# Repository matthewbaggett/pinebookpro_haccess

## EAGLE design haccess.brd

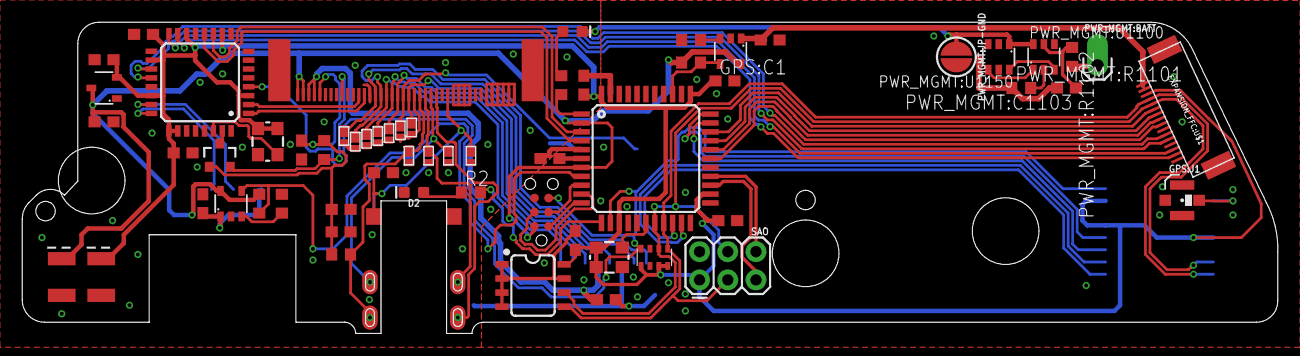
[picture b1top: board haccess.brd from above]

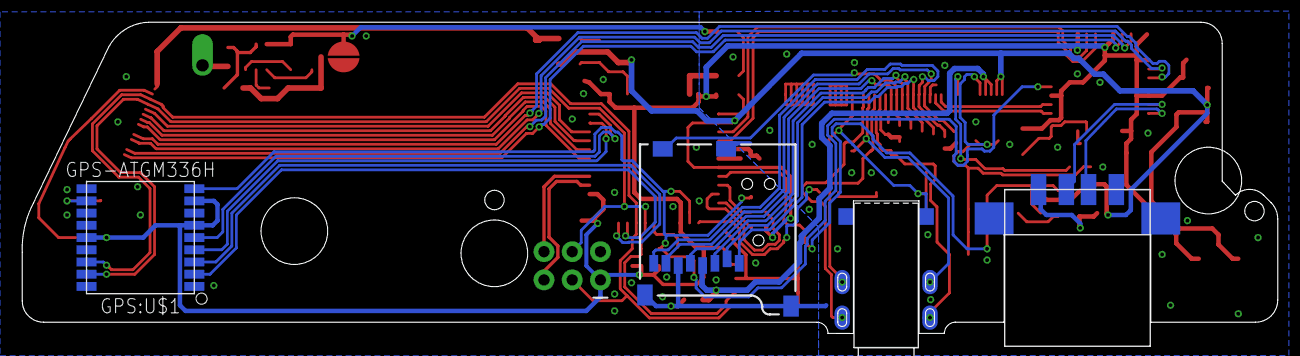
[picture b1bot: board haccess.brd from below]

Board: 2 copper layers, 113.0 x 28.0 mm, 65 parts (4 on the bottom side), 64 nets.

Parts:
D1, D2: LED-0603
EEPROM:C1: 0.1uF; C0603
EEPROM:EEPROM: 24LC256; SO08
EXPANSION_FFC:C1: 0.1uF; C0603
EXPANSION_FFC:R1, EXPANSION_FFC:R2: 10k; R0603
EXPANSION_FFC:U$1: PINEBOOK-PRO-EXPANSION-CONNECTOR; FPC-C528044
EXPANSION_FFC:U$2: CURRENT-LIMITINGSY6280; SOT23-5
GPS:C1: 0.1uF; C0603
GPS:J1: U.FL
GPS:U$1: GPS-ATGM336H; ATGM336H
HALL_EFFECT:C1: 0.1uF; C0603
HALL_EFFECT:R1: 10k; R0603
HALL_EFFECT:U$1: HALL_EFFECT_SENSORTH9245; SOT23-3
HEADPHONE:C1, HEADPHONE:C3: 0.1uF; C0603
HEADPHONE:C2: 1uF; C0603
HEADPHONE:ESD1, HEADPHONE:ESD2, HEADPHONE:ESD3, HEADPHONE:ESD4: DIODE_ESDUAD03C05L01; DFN1608
HEADPHONE:HEADPHONES: C128994; AUDIO_JACK_C128994
HEADPHONE:R1: 12.2k; R0603
MICROSD:C1: 0.1uF; C0603
MICROSD:ESD1, MICROSD:ESD2, MICROSD:ESD3, MICROSD:ESD4, MICROSD:ESD5, MICROSD:ESD6, MICROSD:ESD7: DIODE_ESDUAD03C05L01; DFN1608
MICROSD:JP1: USD-SDIO-SOCKET; MICRO-SD-SOCKET-SDIO
MPU:C3: 1uF; C0603
MPU:C4, MPU:C6: 0.1uF; C0603
MPU:PROGRAM: AVR_PROGRAMMER; TC2030-IDC-NL
MPU:RN2: 10k; EXBV8V
MPU:U2: 32U4; TQFP44
MPU:U$2: OSCILLATOR16MHZ_SHENZEN_SCTF_C87369; CRYSTAL-SMD-3.2X2.5MM
PBP_FFC:J2: FPC05040-17204
PWR_MGMT:BATT: 1X01_OFFSET
PWR_MGMT:C1, PWR_MGMT:C8, PWR_MGMT:C1103: 0.1uF; C0603
PWR_MGMT:C10, PWR_MGMT:C11: 47uF; EIA3528
PWR_MGMT:JP-GND: JUMPER-SMT_2_NO_SILK_ROUND; SMT-JUMPER_2_NO_SILK_ROUND
PWR_MGMT:R1101: 1k; R0603
PWR_MGMT:R1102: 100; R0603
PWR_MGMT:U1100: FS312F-G; SOT23-6
PWR_MGMT:U1150: FS8205; SOT23-6
PWR_MGMT:U$3: REGULATOR; SOT23-3
R1, R2: 160; R0603
SAO: FEMALE 2x3; 2X3
USB_A:C1: 0.1uF; C0603
USB_A:R1, USB_A:R2: 10k; R0603
USB_A:U$1: CURRENT-LIMITINGSY6280; SOT23-5
USB_A:USB: USB_RECESSED_C42620; USB_SOCKET_A_C42620
USB_HUB:C1, USB_HUB:C2: 0.1uF; C0603
USB_HUB:IC1: TUSB2046BVFR; VF_S-PQFP-G32
USB_HUB:U$1: OSCILLATOR6MHZ_SHENZEN_SCTF_C387198; CRYSTAL-SMD-3.2X2.5MM

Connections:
3.3V: EEPROM:C1.1, EEPROM:EEPROM.8, EXPANSION_FFC:U$1.P$14, GPS:C1.1, GPS:U$1.P$6, GPS:U$1.P$8, GPS:U$1.P$14, MPU:C4.1, MPU:C6.1, MPU:RN2.5, MPU:RN2.7, MPU:RN2.8, MPU:U2.14, MPU:U2.24, MPU:U2.34, MPU:U2.44, MPU:U$2.1, MPU:U$2.4, PWR_MGMT:C8.1, PWR_MGMT:C11.A, PWR_MGMT:U$3.2, SAO.1, USB_HUB:C1.1, USB_HUB:C2.1, USB_HUB:IC1.3, USB_HUB:IC1.10, USB_HUB:IC1.14, USB_HUB:IC1.18, USB_HUB:IC1.22, USB_HUB:IC1.25, USB_HUB:IC1.26, USB_HUB:U$1.1, USB_HUB:U$1.4
3V0_CODEC: HALL_EFFECT:C1.1, HALL_EFFECT:R1.2, HALL_EFFECT:U$1.1, HEADPHONE:C2.1, HEADPHONE:C3.1, HEADPHONE:R1.2, PBP_FFC:J2.P$36
3V0_SD: MICROSD:C1.1, MICROSD:JP1.VCC, PBP_FFC:J2.P$37, PBP_FFC:J2.P$38
5V: EXPANSION_FFC:R2.1, EXPANSION_FFC:U$2.5, MPU:PROGRAM.2, MPU:U2.2, MPU:U2.7, PBP_FFC:J2.P$39, PBP_FFC:J2.P$40, PWR_MGMT:C1.1, PWR_MGMT:C10.A, PWR_MGMT:U$3.3, USB_A:R2.1, USB_A:U$1.5
/RST: GPS:U$1.P$9, MPU:PROGRAM.5, MPU:RN2.4, MPU:U2.13, USB_HUB:IC1.4
AUD_STATUS: MPU:U2.12, R2.2
DM0: PBP_FFC:J2.P$29, USB_HUB:IC1.2
DM1: MPU:U2.3, USB_HUB:IC1.11
DM2: EXPANSION_FFC:U$1.P$2, USB_HUB:IC1.15
DM3: EXPANSION_FFC:U$1.P$5, USB_HUB:IC1.19
DM4: USB_A:USB.D-, USB_HUB:IC1.23
DP0: PBP_FFC:J2.P$28, USB_HUB:IC1.1
DP1: MPU:U2.4, USB_HUB:IC1.12
DP2: EXPANSION_FFC:U$1.P$3, USB_HUB:IC1.16
DP3: EXPANSION_FFC:U$1.P$6, USB_HUB:IC1.20
DP4: USB_A:USB.D+, USB_HUB:IC1.24
EXPANSION_FFC:ISET: EXPANSION_FFC:R1.1, EXPANSION_FFC:U$2.3
EXPANSION_FFC:VOUT: EXPANSION_FFC:C1.1, EXPANSION_FFC:U$1.P$15, EXPANSION_FFC:U$1.P$16, EXPANSION_FFC:U$2.1
EXP_EN: EXPANSION_FFC:R2.2, EXPANSION_FFC:U$2.4, MPU:U2.36
G0: EXPANSION_FFC:U$1.P$11, MPU:U2.31
G1: EXPANSION_FFC:U$1.P$10, MPU:U2.30
G2: EXPANSION_FFC:U$1.P$9, MPU:U2.29
G3: EXPANSION_FFC:U$1.P$8, MPU:U2.28
GND: D1.C, D2.C, HALL_EFFECT:C1.2, HALL_EFFECT:U$1.3, HEADPHONE:C1.2, HEADPHONE:C2.2, HEADPHONE:C3.2, HEADPHONE:ESD1.P$1, HEADPHONE:ESD2.P$1, HEADPHONE:ESD3.P$1, HEADPHONE:ESD4.P$1, MICROSD:C1.2, MICROSD:ESD1.P$1, MICROSD:ESD2.P$1, MICROSD:ESD3.P$1, MICROSD:ESD4.P$1, MICROSD:ESD5.P$1, MICROSD:ESD6.P$1, MICROSD:ESD7.P$1, MICROSD:JP1.CD2, MICROSD:JP1.GND, MICROSD:JP1.GND1, MICROSD:JP1.GND3, PBP_FFC:J2.P$1, PBP_FFC:J2.P$2, PBP_FFC:J2.P$3, PBP_FFC:J2.P$4, PBP_FFC:J2.P$5, PBP_FFC:J2.P$6, PBP_FFC:J2.P$9, PBP_FFC:J2.P$10, PBP_FFC:J2.P$11, PBP_FFC:J2.P$12, PBP_FFC:J2.P$14, PBP_FFC:J2.P$19, PBP_FFC:J2.P$27, PBP_FFC:J2.P$30, PBP_FFC:J2.P$41, PBP_FFC:J2.P$42, PWR_MGMT:C1.2, PWR_MGMT:C8.2, PWR_MGMT:C10.C, PWR_MGMT:C11.C, PWR_MGMT:JP-GND.1, PWR_MGMT:U1100.6, PWR_MGMT:U1150.1, PWR_MGMT:U$3.1, USB_A:C1.2, USB_A:R1.2, USB_A:U$1.2, USB_A:USB.GND, USB_HUB:C1.2, USB_HUB:C2.2, USB_HUB:IC1.7, USB_HUB:IC1.27, USB_HUB:IC1.28, USB_HUB:IC1.31, USB_HUB:U$1.2
GND_ISOLATED: EEPROM:C1.2, EEPROM:EEPROM.1, EEPROM:EEPROM.2, EEPROM:EEPROM.3, EEPROM:EEPROM.4, EEPROM:EEPROM.7, EXPANSION_FFC:C1.2, EXPANSION_FFC:R1.2, EXPANSION_FFC:U$1.P$1, EXPANSION_FFC:U$1.P$4, EXPANSION_FFC:U$1.P$7, EXPANSION_FFC:U$1.SHIELD1, EXPANSION_FFC:U$1.SHIELD2, EXPANSION_FFC:U$2.2, GPS:C1.2, GPS:J1.1, GPS:J1.2, GPS:U$1.P$1, GPS:U$1.P$10, GPS:U$1.P$12, MPU:C3.2, MPU:C4.2, MPU:C6.2, MPU:PROGRAM.6, MPU:RN2.3, MPU:RN2.6, MPU:U2.5, MPU:U2.15, MPU:U2.23, MPU:U2.35, MPU:U2.43, MPU:U$2.2, PWR_MGMT:C1103.2, PWR_MGMT:JP-GND.2, PWR_MGMT:R1101.1, PWR_MGMT:U1150.3, SAO.2
GPS:RF_IN: GPS:J1.FEED, GPS:U$1.P$11
GPS_ENABLE: GPS:U$1.P$5, MPU:U2.33
HALL_SENSE: HALL_EFFECT:R1.1, HALL_EFFECT:U$1.2, PBP_FFC:J2.P$32
HPO_L: HEADPHONE:ESD2.P$2, HEADPHONE:HEADPHONES.B2, HEADPHONE:HEADPHONES.T2, PBP_FFC:J2.P$16
HPO_R: HEADPHONE:ESD3.P$2, HEADPHONE:HEADPHONES.B6, HEADPHONE:HEADPHONES.T6, PBP_FFC:J2.P$17
HP_DET_H: HEADPHONE:C1.1, HEADPHONE:ESD1.P$2, HEADPHONE:HEADPHONES.B3, HEADPHONE:HEADPHONES.T3, PBP_FFC:J2.P$13
HP_GND: HEADPHONE:HEADPHONES.B4, HEADPHONE:HEADPHONES.T4, PBP_FFC:J2.P$15
MIC_IN2P: HEADPHONE:ESD4.P$2, HEADPHONE:HEADPHONES.B1, HEADPHONE:HEADPHONES.T1, HEADPHONE:R1.1, PBP_FFC:J2.P$18
MPU:32U4_OSC: MPU:U2.17, MPU:U$2.3
MPU:PB1/SCK: MPU:PROGRAM.3, MPU:U2.9
MPU:PB2/MOSI: MPU:PROGRAM.4, MPU:U2.10
MPU:PB3/MISO: MPU:PROGRAM.1, MPU:U2.11
MPU:UCAP: MPU:C3.1, MPU:U2.6
MPU_RX: GPS:U$1.P$2, MPU:U2.20
MPU_TX: GPS:U$1.P$3, MPU:U2.21
unnamed: D1.A, R1.1
unnamed: D2.A, R2.1
PULSE: GPS:U$1.P$4, MPU:U2.32
PWR_MGMT:FS_CS: PWR_MGMT:R1101.2, PWR_MGMT:U1100.2
PWR_MGMT:FS_V_BATT: PWR_MGMT:C1103.1, PWR_MGMT:R1102.1, PWR_MGMT:U1100.5
PWR_MGMT:OC: PWR_MGMT:U1100.3, PWR_MGMT:U1150.6
PWR_MGMT:OD: PWR_MGMT:U1100.1, PWR_MGMT:U1150.4
SAO1: MPU:U2.25, SAO.5
SAO2: MPU:U2.26, SAO.6
SCL: EEPROM:EEPROM.6, EXPANSION_FFC:U$1.P$12, GPS:U$1.P$17, MPU:RN2.2, MPU:U2.18, SAO.4
SDA: EEPROM:EEPROM.5, EXPANSION_FFC:U$1.P$13, GPS:U$1.P$16, MPU:RN2.1, MPU:U2.19, SAO.3
SD_CLK: MICROSD:ESD4.P$2, MICROSD:JP1.CLK, PBP_FFC:J2.P$20
SD_CMD: MICROSD:ESD5.P$2, MICROSD:JP1.CMD, PBP_FFC:J2.P$22
SD_D0: MICROSD:ESD3.P$2, MICROSD:JP1.DAT0, PBP_FFC:J2.P$26
SD_D1: MICROSD:ESD2.P$2, MICROSD:JP1.DAT1, PBP_FFC:J2.P$25
SD_D2: MICROSD:ESD7.P$2, MICROSD:JP1.DAT2, PBP_FFC:J2.P$24
SD_D3: MICROSD:ESD6.P$2, MICROSD:JP1.CD/DAT3, PBP_FFC:J2.P$23
SD_DET_L: MICROSD:ESD1.P$2, MICROSD:JP1.CD1, PBP_FFC:J2.P$21
STATUS: MPU:U2.1, R1.2
USB_A:ISET: USB_A:R1.1, USB_A:U$1.3
USB_A:VOUT: USB_A:C1.1, USB_A:U$1.1, USB_A:USB.VCC
USB_EN: MPU:U2.8, USB_A:R2.2, USB_A:U$1.4
USB_HUB:N$1: USB_HUB:IC1.30, USB_HUB:U$1.3
V_BATT: PWR_MGMT:BATT.1, PWR_MGMT:R1102.2

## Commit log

2020-11-16 Initial commit of board outline and partially placed parts. Need to find an audio jack that fits + GPS controller + extensible headers + service LED.
2020-11-17 Think I'm done?
2020-11-17 I think I'm done?
2020-11-21 More revisioning.. Now has always-available power.. but its not completed. Daughterboard dimensions completed.

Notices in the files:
parts and their libraries:
SparkFun-Retired: Licensing: Creative Commons ShareAlike 4.0 International - https://creativecommons.org/licenses/by-sa/4.0
